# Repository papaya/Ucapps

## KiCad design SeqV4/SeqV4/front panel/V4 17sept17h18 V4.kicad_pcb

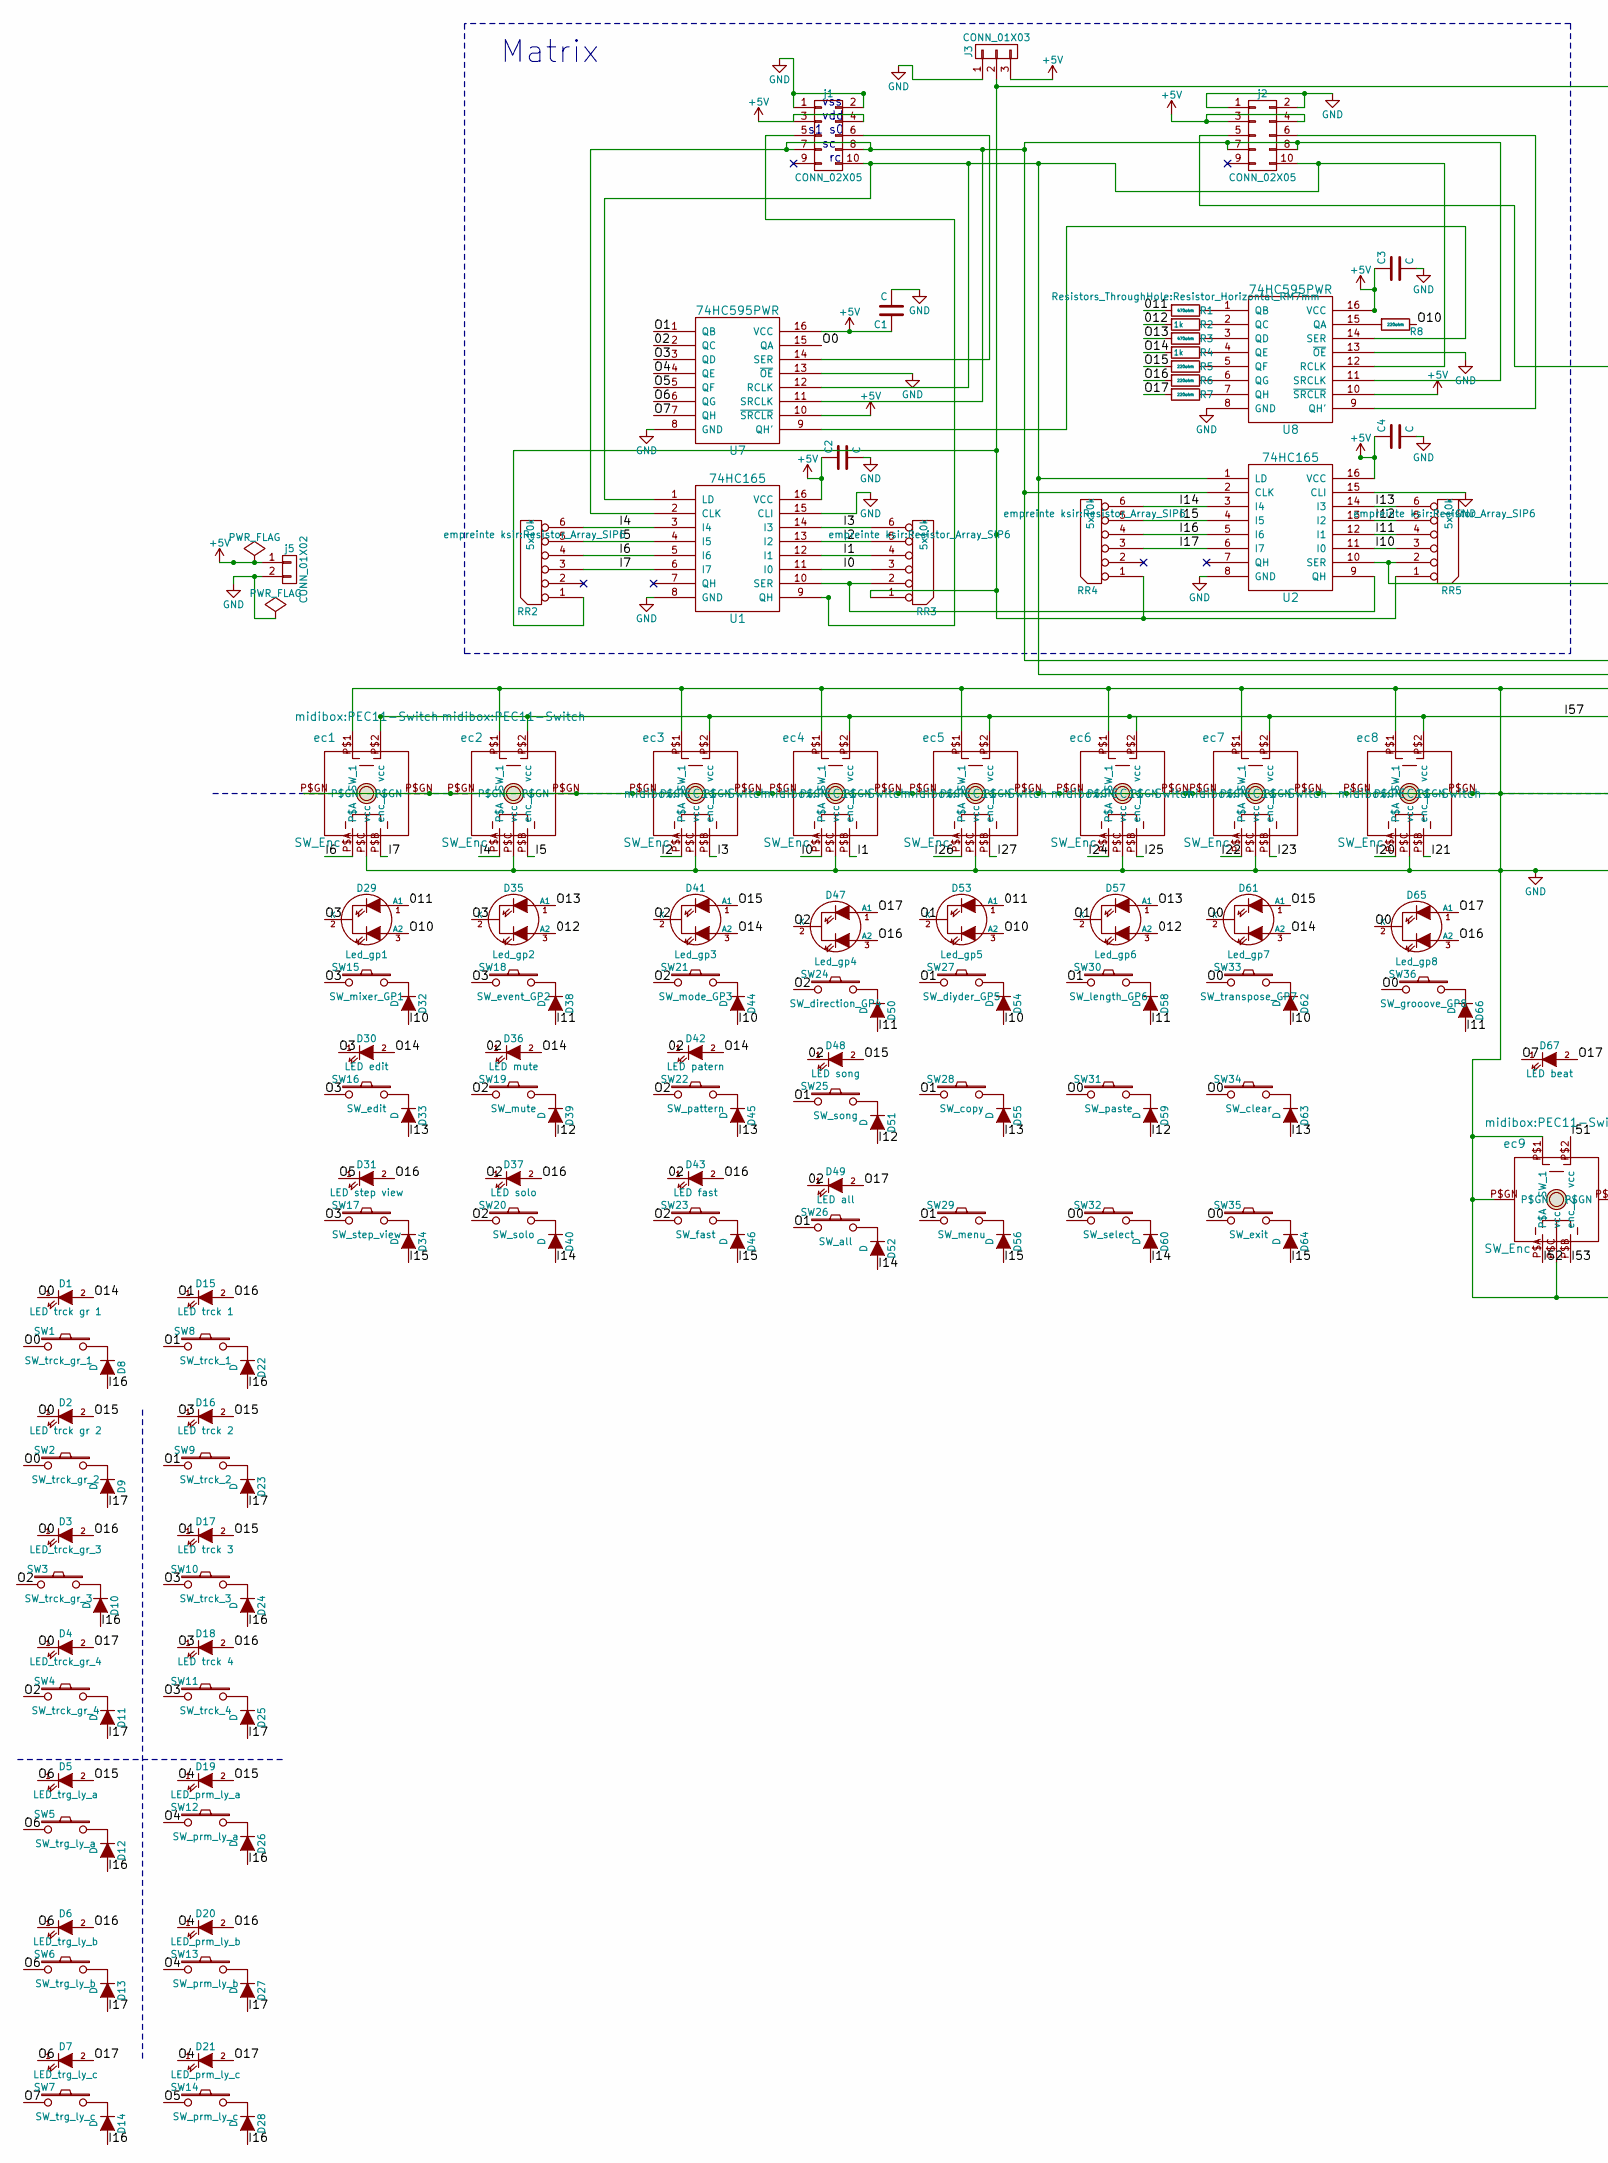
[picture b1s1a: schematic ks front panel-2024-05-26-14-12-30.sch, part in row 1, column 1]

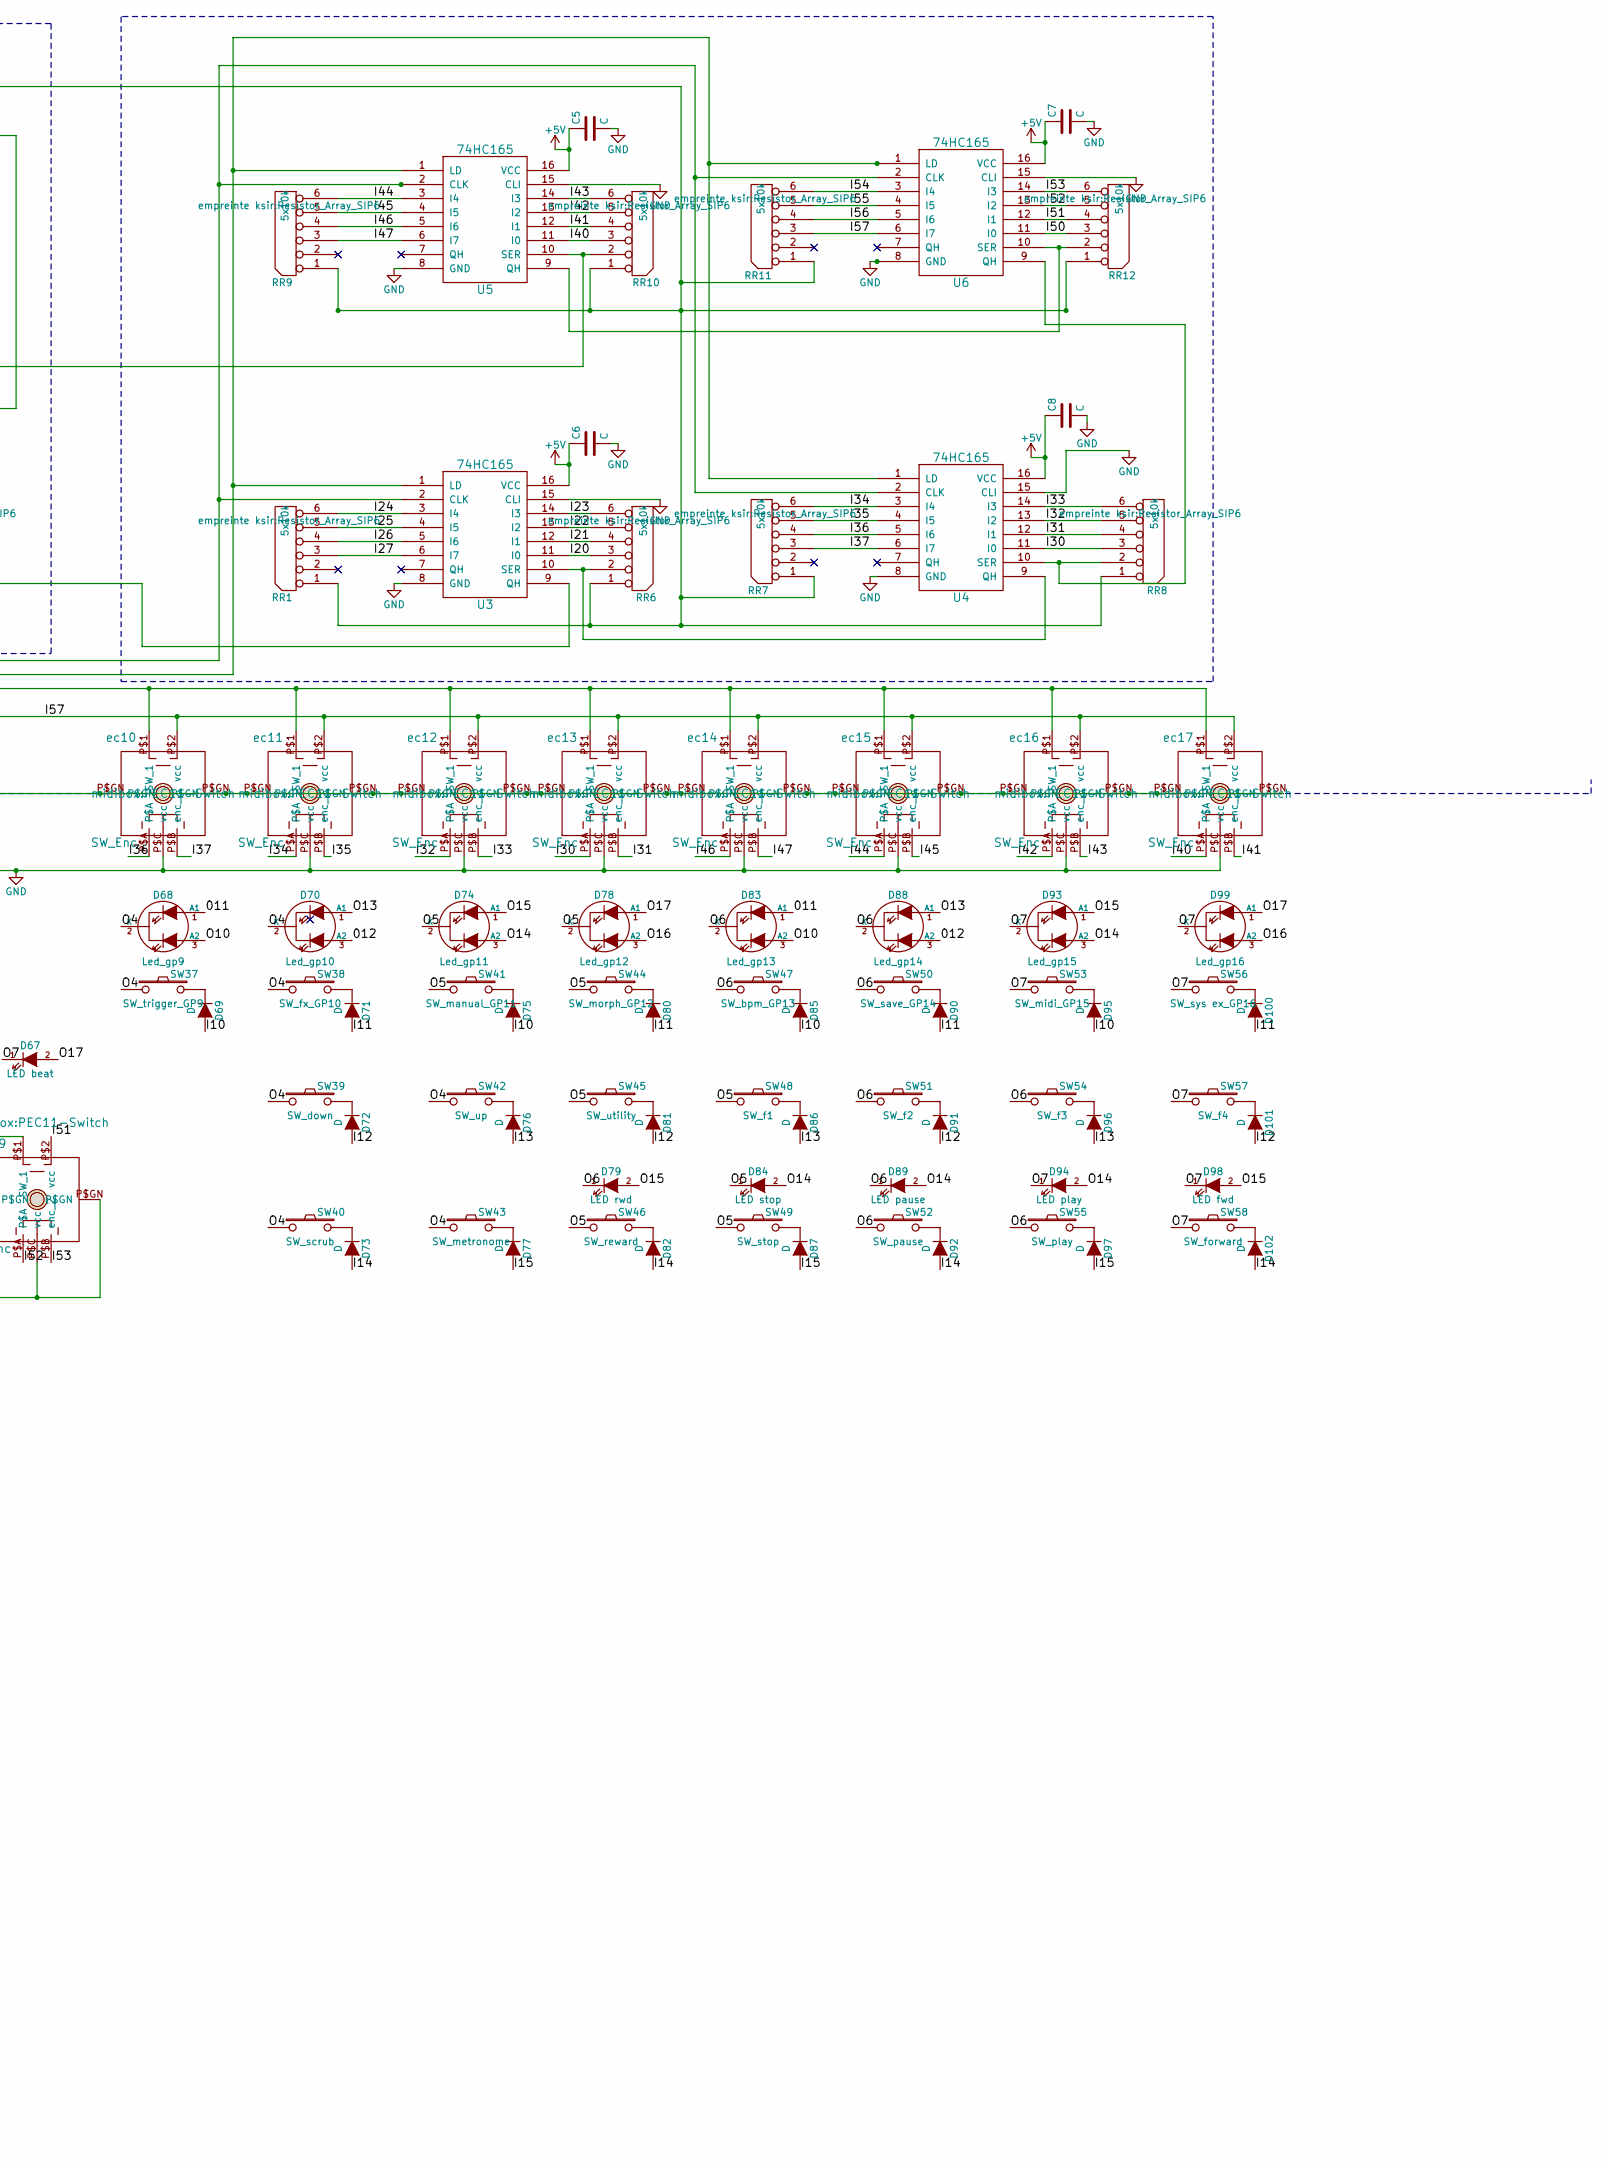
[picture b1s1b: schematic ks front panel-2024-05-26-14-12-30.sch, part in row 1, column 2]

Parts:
C1, C2, C3, C4, C5, C6, C7, C8: C; C_Disc_D6_P5
D1: LED trck gr 1; LED-3MM
D2: LED trck gr 2; LED-3MM
D3: LED_trck_gr_3; LED-3MM
D4: LED_trck_gr_4; LED-3MM
D5: LED_trg_ly_a; LED-3MM
D6: LED_trg_ly_b; LED-3MM
D7: LED_trg_ly_c; LED-3MM
D8, D9, D10, D11, D12, D13, D14, D22, D23, D24, D25, D26, D27, D28, D32, D33, D34, D38, D39, D40, D44, D45, D46, D50, D51, D52, D54, D55, D56, D58, D59, D60, D62, D63, D64, D66, D69, D71, D72, D73, D75, D76, D77, D80, D81, D82, D85, D86, D87, D90, D91, D92, D95, D96, D97, D100, D101, D102: D; Diode_DO-35_SOD27_Horizontal_RM10
D15: LED trck 1; LED-3MM
D16: LED trck 2; LED-3MM
D17: LED trck 3; LED-3MM
D18: LED trck 4; LED-3MM
D19: LED_prm_ly_a; LED-3MM
D20: LED_prm_ly_b; LED-3MM
D21: LED_prm_ly_c; LED-3MM
D29: Led_gp1; LED-5MM-3
D30: LED edit; LED-3MM
D31: LED step view; LED-3MM
D35: Led_gp2; LED-5MM-3
D36: LED mute; LED-3MM
D37: LED solo; LED-3MM
D41: Led_gp3; LED-5MM-3
D42: LED patern; LED-3MM
D43: LED fast; LED-3MM
D47: Led_gp4; LED-5MM-3
D48: LED song; LED-3MM
D49: LED all; LED-3MM
D53: Led_gp5; LED-5MM-3
D57: Led_gp6; LED-5MM-3
D61: Led_gp7; LED-5MM-3
D65: Led_gp8; LED-5MM-3
D67: LED beat; LED-3MM
D68: Led_gp9; LED-5MM-3
D70: Led_gp10; LED-5MM-3
D74: Led_gp11; LED-5MM-3
D78: Led_gp12; LED-5MM-3
D79: LED rwd; LED-3MM
D83: Led_gp13; LED-5MM-3
D84: LED stop; LED-3MM
D88: Led_gp14; LED-5MM-3
D89: LED pause; LED-3MM
D93: Led_gp15; LED-5MM-3
D94: LED play; LED-3MM
D98: LED fwd; LED-3MM
D99: Led_gp16; LED-5MM-3
J3: CONN_01X03; Pin_Header_Straight_1x03
R1, R3: 470ohm; Resistor_Horizontal_RM7mm
R2, R4: 1k; Resistor_Horizontal_RM7mm
R5, R6, R7, R8: 220ohm; Resistor_Horizontal_RM7mm
RR1, RR2, RR3, RR4, RR5, RR6, RR7, RR8, RR9, RR10, RR11, RR12: 5x10k; Resistor_Array_SIP6
SW1: SW_trck_gr_1; Tact6mm-PanasonicLTS
SW2: SW_trck_gr_2; Tact6mm-PanasonicLTS
SW3: SW_trck_gr_3; Tact6mm-PanasonicLTS
SW4: SW_trck_gr_4; Tact6mm-PanasonicLTS
SW5: SW_trg_ly_a; Tact6mm-PanasonicLTS
SW6: SW_trg_ly_b; Tact6mm-PanasonicLTS
SW7: SW_trg_ly_c; Tact6mm-PanasonicLTS
SW8: SW_trck_1; Tact6mm-PanasonicLTS
SW9: SW_trck_2; Tact6mm-PanasonicLTS
SW10: SW_trck_3; Tact6mm-PanasonicLTS
SW11: SW_trck_4; Tact6mm-PanasonicLTS
SW12: SW_prm_ly_a; Tact6mm-PanasonicLTS
SW13: SW_prm_ly_b; Tact6mm-PanasonicLTS
SW14: SW_prm_ly_c; Tact6mm-PanasonicLTS
SW15: SW_mixer_GP1; Tact6mm-PanasonicLTS
SW16: SW_edit; Tact6mm-PanasonicLTS
SW17: SW_step_view; Tact6mm-PanasonicLTS
SW18: SW_event_GP2; Tact6mm-PanasonicLTS
SW19: SW_mute; Tact6mm-PanasonicLTS
SW20: SW_solo; Tact6mm-PanasonicLTS
SW21: SW_mode_GP3; Tact6mm-PanasonicLTS
SW22: SW_pattern; Tact6mm-PanasonicLTS
SW23: SW_fast; Tact6mm-PanasonicLTS
SW24: SW_direction_GP4; Tact6mm-PanasonicLTS
SW25: SW_song; Tact6mm-PanasonicLTS
SW26: SW_all; Tact6mm-PanasonicLTS
SW27: SW_diyder_GP5; Tact6mm-PanasonicLTS
SW28: SW_copy; Tact6mm-PanasonicLTS
SW29: SW_menu; Tact6mm-PanasonicLTS
SW30: SW_length_GP6; Tact6mm-PanasonicLTS
SW31: SW_paste; Tact6mm-PanasonicLTS
SW32: SW_select; Tact6mm-PanasonicLTS
SW33: SW_transpose_GP7; Tact6mm-PanasonicLTS
SW34: SW_clear; Tact6mm-PanasonicLTS
SW35: SW_exit; Tact6mm-PanasonicLTS
SW36: SW_grooove_GP8; Tact6mm-PanasonicLTS
SW37: SW_trigger_GP9; Tact6mm-PanasonicLTS
SW38: SW_fx_GP10; Tact6mm-PanasonicLTS
SW39: SW_down; Tact6mm-PanasonicLTS
SW40: SW_scrub; Tact6mm-PanasonicLTS
SW41: SW_manual_GP11; Tact6mm-PanasonicLTS
SW42: SW_up; Tact6mm-PanasonicLTS
SW43: SW_metronome; Tact6mm-PanasonicLTS
SW44: SW_morph_GP12; Tact6mm-PanasonicLTS
SW45: SW_utility; Tact6mm-PanasonicLTS
SW46: SW_reward; Tact6mm-PanasonicLTS
SW47: SW_bpm_GP13; Tact6mm-PanasonicLTS
SW48: SW_f1; Tact6mm-PanasonicLTS
SW49: SW_stop; Tact6mm-PanasonicLTS
SW50: SW_save_GP14; Tact6mm-PanasonicLTS
SW51: SW_f2; Tact6mm-PanasonicLTS
SW52: SW_pause; Tact6mm-PanasonicLTS
SW53: SW_midi_GP15; Tact6mm-PanasonicLTS
SW54: SW_f3; Tact6mm-PanasonicLTS
SW55: SW_play; Tact6mm-PanasonicLTS
SW56: SW_sys ex_GP16; Tact6mm-PanasonicLTS
SW57: SW_f4; Tact6mm-PanasonicLTS
SW58: SW_forward; Tact6mm-PanasonicLTS
U1, U2, U3, U4, U5, U6: 74HC165; DIP-16_W7.62mm
U7, U8: 74HC595PWR; DIP-16_W7.62mm
ec1, ec2, ec3, ec4, ec5, ec6, ec7, ec8, ec9, ec10, ec11, ec12, ec13, ec14, ec15, ec16, ec17: SW_Enc; PEC11-Switch
j1, j2: CONN_02X05; vasch_strip_5x2
j5: CONN_01X02; PINHEAD1-2

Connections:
+5V: C1.1, C2.1, C3.1, C4.1, C5.1, C6.1, C7.1, C8.1, J3.3, U1.16 (VCC), U2.16 (VCC), U3.16 (VCC), U4.16 (VCC), U5.16 (VCC), U6.16 (VCC), U7.10 (~SRCLR~), U7.16 (VCC), U8.10 (~SRCLR~), U8.16 (VCC), j1.3, j1.4, j2.3, j2.4, j5.1; also elsewhere on the board
/02: D36.1 (K), D42.1 (K), D43.1 (K), D48.1 (K), D49.1 (K), U7.2 (QC)
/011: D29.1 (A1), D53.1 (A1), D68.1 (A1), D83.1 (A1), R1.2
/012: D35.3 (A2), D57.3 (A2), D70.3 (A2), D88.3 (A2), R2.2
/I0: RR3.3, U1.11 (I0), ec4.P$A
/I1: RR3.4, U1.12 (I1), ec4.P$B (enc_2)
/I2: RR3.5, U1.13 (I2), ec3.P$A
/I3: RR3.6, U1.14 (I3), ec3.P$B (enc_2)
/I4: RR2.6, U1.3 (I4), ec2.P$A
/I5: RR2.5, U1.4 (I5), ec2.P$B (enc_2)
/I6: RR2.4, U1.5 (I6), ec1.P$A
/I7: RR2.3, U1.6 (I7), ec1.P$B (enc_2)
/I10: D32.2 (A), D44.2 (A), D54.2 (A), D62.2 (A), D69.2 (A), D75.2 (A), D85.2 (A), D95.2 (A), RR5.3, U2.11 (I0)
/I11: D38.2 (A), D50.2 (A), D58.2 (A), D66.2 (A), D71.2 (A), D80.2 (A), D90.2 (A), D100.2 (A), RR5.4, U2.12 (I1)
/I12: D39.2 (A), D51.2 (A), D59.2 (A), D72.2 (A), D81.2 (A), D91.2 (A), D101.2 (A), RR5.5, U2.13 (I2)
/I13: D33.2 (A), D45.2 (A), D55.2 (A), D63.2 (A), D76.2 (A), D86.2 (A), D96.2 (A), RR5.6, U2.14 (I3)
/I14: D40.2 (A), D52.2 (A), D60.2 (A), D73.2 (A), D82.2 (A), D92.2 (A), D102.2 (A), RR4.6, U2.3 (I4)
/I15: D34.2 (A), D46.2 (A), D56.2 (A), D64.2 (A), D77.2 (A), D87.2 (A), D97.2 (A), RR4.5, U2.4 (I5)
/I16: D8.2 (A), D10.2 (A), D12.2 (A), D14.2 (A), D22.2 (A), D24.2 (A), D26.2 (A), D28.2 (A), RR4.4, U2.5 (I6)
/I17: D9.2 (A), D11.2 (A), D13.2 (A), D23.2 (A), D25.2 (A), D27.2 (A), RR4.3, U2.6 (I7)
/I20: RR6.3, U3.11 (I0), ec8.P$A
/I21: RR6.4, U3.12 (I1), ec8.P$B (enc_2)
/I22: RR6.5, U3.13 (I2), ec7.P$A
/I23: RR6.6, U3.14 (I3), ec7.P$B (enc_2)
/I24: RR1.6, U3.3 (I4), ec6.P$A
/I25: RR1.5, U3.4 (I5), ec6.P$B (enc_2)
/I26: RR1.4, U3.5 (I6), ec5.P$A
/I27: RR1.3, U3.6 (I7), ec5.P$B (enc_2)
/I30: RR8.3, U4.11 (I0), ec13.P$A
/I31: RR8.4, U4.12 (I1), ec13.P$B (enc_2)
/I32: RR8.5, U4.13 (I2), ec12.P$A
/I33: RR8.6, U4.14 (I3), ec12.P$B (enc_2)
/I34: RR7.6, U4.3 (I4), ec11.P$A
/I35: RR7.5, U4.4 (I5), ec11.P$B (enc_2)
/I36: RR7.4, U4.5 (I6), ec10.P$A
/I37: RR7.3, U4.6 (I7), ec10.P$B (enc_2)
/I40: RR10.3, U5.11 (I0), ec17.P$A
/I41: RR10.4, U5.12 (I1), ec17.P$B (enc_2)
/I42: RR10.5, U5.13 (I2), ec16.P$A
/I43: RR10.6, U5.14 (I3), ec16.P$B (enc_2)
/I44: RR9.6, U5.3 (I4), ec15.P$A
/I45: RR9.5, U5.4 (I5), ec15.P$B (enc_2)
/I46: RR9.4, U5.5 (I6), ec14.P$A
/I47: RR9.3, U5.6 (I7), ec14.P$B (enc_2)
/I50: RR12.3, U6.11 (I0)
/I51: RR12.4, U6.12 (I1), ec9.P$2 (vcc)
/I52: RR12.5, U6.13 (I2), ec9.P$A
/I53: RR12.6, U6.14 (I3), ec9.P$B (enc_2)
/I54: RR11.6, U6.3 (I4)
/I55: RR11.5, U6.4 (I5)
/I56: RR11.4, U6.5 (I6)
/I57: RR11.3, U6.6 (I7), ec1.P$2 (vcc), ec2.P$2 (vcc), ec3.P$2 (vcc), ec4.P$2 (vcc), ec5.P$2 (vcc), ec6.P$2 (vcc), ec7.P$2 (vcc), ec8.P$2 (vcc), ec10.P$2 (vcc), ec11.P$2 (vcc), ec12.P$2 (vcc), ec13.P$2 (vcc), ec14.P$2 (vcc), ec15.P$2 (vcc), ec16.P$2 (vcc), ec17.P$2 (vcc)
/O0: D1.1 (K), D2.1 (K), D3.1 (K), D4.1 (K), D61.2 (K), D65.2 (K), SW1.2, SW2.2, SW31.2, SW32.2, SW33.2, SW34.2, SW35.2, SW36.2, U7.15 (QA)
/O1: D15.1 (K), D17.1 (K), D53.2 (K), D57.2 (K), SW8.2, SW9.2, SW25.2, SW26.2, SW27.2, SW28.2, SW29.2, SW30.2, U7.1 (QB)
/O2: D37.1 (K), D41.2 (K), D47.2 (K), SW3.2, SW4.2, SW19.2, SW20.2, SW21.2, SW22.2, SW23.2, SW24.2
/O3: D16.1 (K), D18.1 (K), D29.2 (K), D30.1 (K), D35.2 (K), SW10.2, SW11.2, SW15.2, SW16.2, SW17.2, SW18.2, U7.3 (QD)
/O4: D19.1 (K), D20.1 (K), D21.1 (K), D68.2 (K), D70.2 (K), SW12.2, SW13.2, SW37.1, SW38.1, SW39.1, SW40.1, SW42.1, SW43.1, U7.4 (QE)
/O5: D31.1 (K), D74.2 (K), D78.2 (K), D84.1 (K), SW14.2, SW41.1, SW44.1, SW45.1, SW46.1, SW48.1, SW49.1, U7.5 (QF)
/O6: D5.1 (K), D6.1 (K), D7.1 (K), D79.1 (K), D83.2 (K), D88.2 (K), D89.1 (K), SW5.2, SW6.2, SW47.1, SW50.1, SW51.1, SW52.1, SW54.1, SW55.1, U7.6 (QG)
/O7: D67.1 (K), D93.2 (K), D94.1 (K), D98.1 (K), D99.2 (K), SW7.2, SW53.1, SW56.1, SW57.1, SW58.1, U7.7 (QH)
/O10: D29.3 (A2), D53.3 (A2), D68.3 (A2), D83.3 (A2), R8.1
/O13: D35.1 (A1), D57.1 (A1), D70.1 (A1), D88.1 (A1), R3.2
/O14: D1.2 (A), D30.2 (A), D36.2 (A), D41.3 (A2), D42.2 (A), D61.3 (A2), D74.3 (A2), D84.2 (A), D89.2 (A), D93.3 (A2), D94.2 (A), R4.2
/O15: D2.2 (A), D5.2 (A), D16.2 (A), D17.2 (A), D19.2 (A), D41.1 (A1), D48.2 (A), D61.1 (A1), D74.1 (A1), D79.2 (A), D93.1 (A1), D98.2 (A), R5.2
/O16: D3.2 (A), D6.2 (A), D15.2 (A), D18.2 (A), D20.2 (A), D31.2 (A), D37.2 (A), D43.2 (A), D47.3 (A2), D65.3 (A2), D78.3 (A2), D99.3 (A2), R6.2
/O17: D4.2 (A), D7.2 (A), D21.2 (A), D47.1 (A1), D49.2 (A), D65.1 (A1), D67.2 (A), D78.1 (A1), D99.1 (A1), R7.2
unnamed: D8.1 (K), SW1.1
unnamed: D9.1 (K), SW2.1
unnamed: D10.1 (K), SW3.1
unnamed: D11.1 (K), SW4.1
unnamed: D12.1 (K), SW5.1
unnamed: D13.1 (K), SW6.1
unnamed: D14.1 (K), SW7.1
unnamed: D22.1 (K), SW8.1
unnamed: D23.1 (K), SW9.1
unnamed: D24.1 (K), SW10.1
unnamed: D25.1 (K), SW11.1
unnamed: D26.1 (K), SW12.1
unnamed: D27.1 (K), SW13.1
unnamed: D28.1 (K), SW14.1
unnamed: D32.1 (K), SW15.1
unnamed: D33.1 (K), SW16.1
unnamed: D34.1 (K), SW17.1
unnamed: D38.1 (K), SW18.1
unnamed: D39.1 (K), SW19.1
unnamed: D40.1 (K), SW20.1
unnamed: D44.1 (K), SW21.1
unnamed: D45.1 (K), SW22.1
unnamed: D46.1 (K), SW23.1
unnamed: D50.1 (K), SW24.1
unnamed: D51.1 (K), SW25.1
unnamed: D52.1 (K), SW26.1
unnamed: D54.1 (K), SW27.1
unnamed: D55.1 (K), SW28.1
unnamed: D56.1 (K), SW29.1
unnamed: D58.1 (K), SW30.1
unnamed: D59.1 (K), SW31.1
unnamed: D60.1 (K), SW32.1
unnamed: D62.1 (K), SW33.1
unnamed: D63.1 (K), SW34.1
unnamed: D64.1 (K), SW35.1
unnamed: D66.1 (K), SW36.1
unnamed: D69.1 (K), SW37.2
unnamed: D71.1 (K), SW38.2
unnamed: D72.1 (K), SW39.2
unnamed: D73.1 (K), SW40.2
unnamed: D75.1 (K), SW41.2
unnamed: D76.1 (K), SW42.2
unnamed: D77.1 (K), SW43.2
unnamed: D80.1 (K), SW44.2
unnamed: D81.1 (K), SW45.2
unnamed: D82.1 (K), SW46.2
unnamed: D85.1 (K), SW47.2
unnamed: D86.1 (K), SW48.2
unnamed: D87.1 (K), SW49.2
unnamed: D90.1 (K), SW50.2
unnamed: D91.1 (K), SW51.2
unnamed: D92.1 (K), SW52.2
unnamed: D95.1 (K), SW53.2
unnamed: D96.1 (K), SW54.2
unnamed: D97.1 (K), SW55.2
unnamed: D100.1 (K), SW56.2
unnamed: D101.1 (K), SW57.2
unnamed: D102.1 (K), SW58.2
unnamed: J3.2, RR1.1 (COM), RR2.1 (COM), RR3.1 (COM), RR4.1 (COM), RR5.1 (COM), RR6.1 (COM), RR7.1 (COM), RR8.1 (COM), RR9.1 (COM), RR10.1 (COM), RR11.1 (COM), RR12.1 (COM)
unnamed: R1.1, U8.1 (QB)
unnamed: R2.1, U8.2 (QC)
unnamed: R3.1, U8.3 (QD)
unnamed: R4.1, U8.4 (QE)
unnamed: R5.1, U8.5 (QF)
unnamed: R6.1, U8.6 (QG)
unnamed: R7.1, U8.7 (QH)
unnamed: R8.2, U8.15 (QA)
unnamed: RR3.2, U1.10 (SER), U2.9 (QH)
unnamed: RR5.2, U2.10 (SER), U3.9 (QH)
unnamed: RR6.2, U3.10 (SER), U4.9 (QH)
unnamed: RR8.2, U4.10 (SER), U6.9 (QH)
unnamed 137: RR10.2, U5.10 (SER), j2.5; also elsewhere on the board
unnamed: RR12.2, U5.9 (QH), U6.10 (SER)
unnamed 139: U1.1 (LD), U2.1 (LD), U3.1 (LD), U4.1 (LD), U5.1 (LD), U6.1 (LD), U7.12 (RCLK), U8.12 (RCLK), j1.10, j2.10; also elsewhere on the board
unnamed 140: U1.2 (CLK), U2.2 (CLK), U3.2 (CLK), U4.2 (CLK), U5.2 (CLK), U6.2 (CLK), U7.11 (SRCLK), U8.11 (SRCLK), j1.7, j1.8, j2.7, j2.8; also elsewhere on the board
unnamed 141: U1.9 (QH), j1.5; also elsewhere on the board
unnamed: U7.9 (QH'), U8.14 (SER)
unnamed 143: U7.14 (SER), j1.6; also elsewhere on the board
unnamed 144: U8.9 (QH'), j2.6; also elsewhere on the board

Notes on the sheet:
Matrix
vss
vdd

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
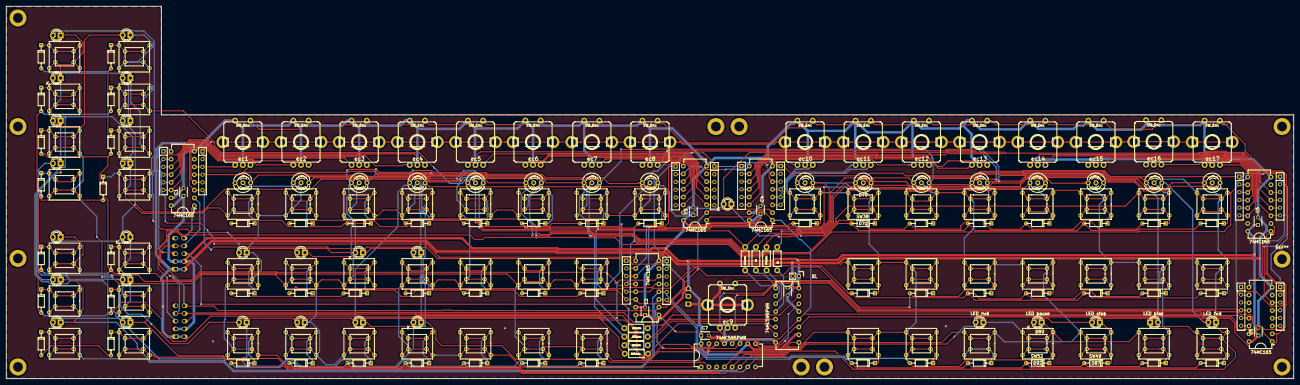
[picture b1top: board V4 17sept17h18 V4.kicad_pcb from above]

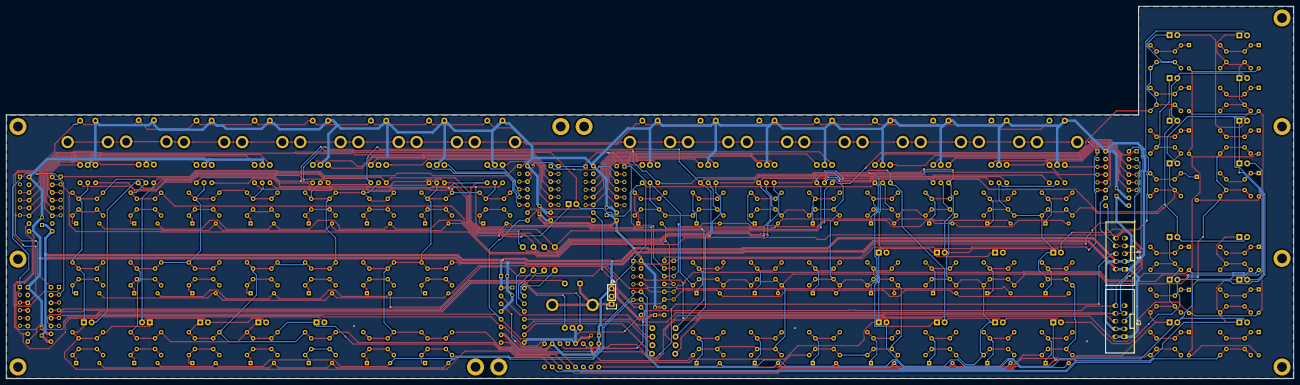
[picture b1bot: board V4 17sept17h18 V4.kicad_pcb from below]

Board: 2 copper layers, 421.6 x 121.9 mm, 217 parts (3 on the bottom side), 147 nets.

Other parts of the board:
J2: CONN_02X05; vasch_strip_5x2
J 1: CONN_02X05; vasch_strip_5x2

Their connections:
+5V: J2.3, J2.4, J 1.3, J 1.4; also elsewhere on the board
unnamed 137: J2.5; also elsewhere on the board
unnamed 139: J2.10, J 1.10; also elsewhere on the board
unnamed 140: J2.7, J2.8, J 1.7, J 1.8; also elsewhere on the board
unnamed 141: J 1.5; also elsewhere on the board
unnamed 143: J 1.6; also elsewhere on the board
unnamed 144: J2.6; also elsewhere on the board
